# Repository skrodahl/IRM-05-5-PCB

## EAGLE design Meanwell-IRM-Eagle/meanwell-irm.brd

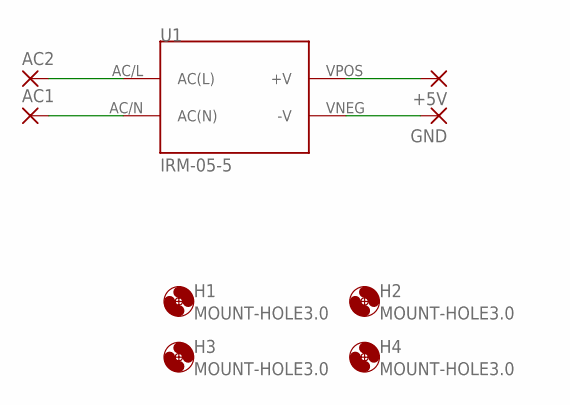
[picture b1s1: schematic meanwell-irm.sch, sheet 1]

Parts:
+5V: 3,81/1,4
AC1, AC2: 3,81/1,4
GND: 3,81/1,4
H1, H2, H3, H4: MOUNT-HOLE3.0; 3,0
U1: IRM-05-5; CONV_IRM-05-5

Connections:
unnamed: AC2.1, U1.AC/L (AC(L))
unnamed: AC1.1, U1.AC/N (AC(N))
unnamed: +5V.1, U1.VPOS (+V)
unnamed: GND.1, U1.VNEG (-V)

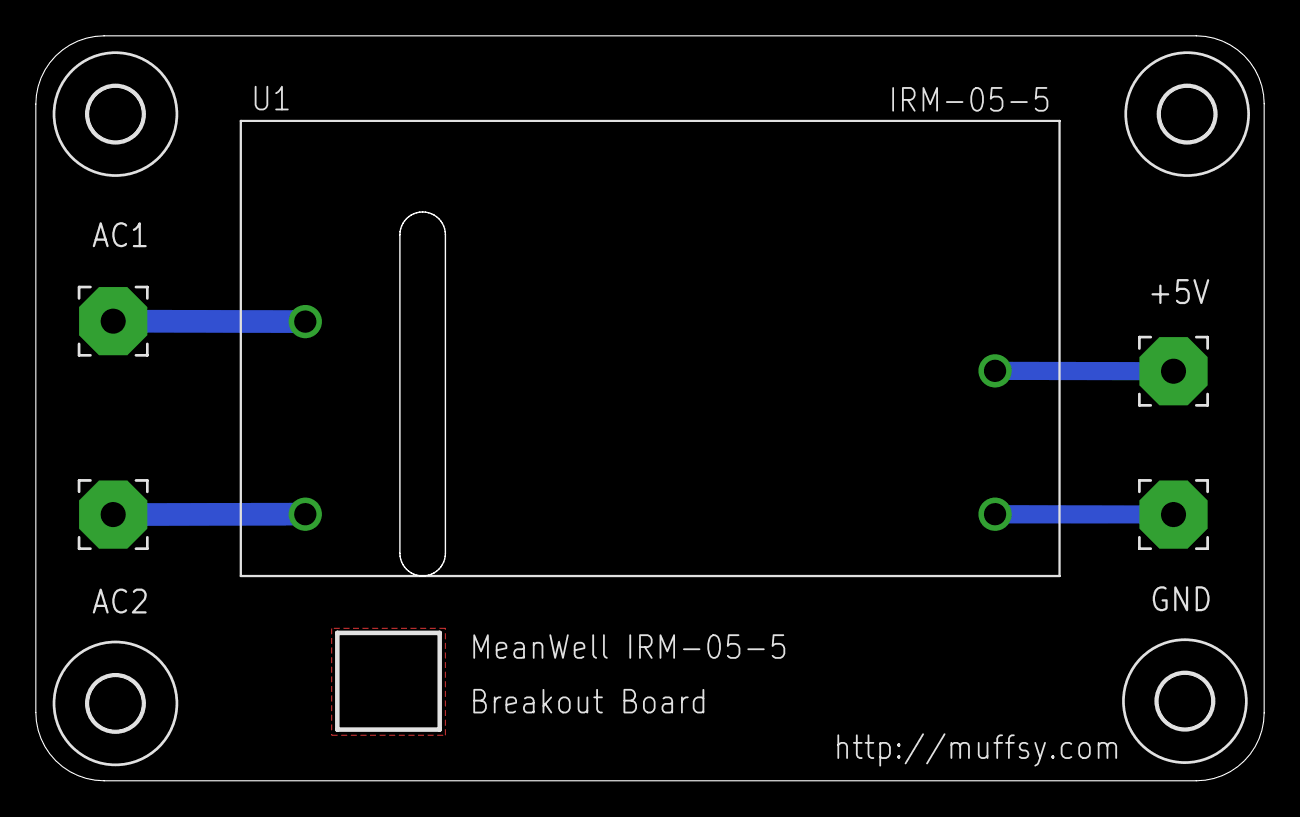
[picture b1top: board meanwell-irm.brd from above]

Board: 2 copper layers, 68.5 x 41.5 mm, 9 parts (0 on the bottom side), 4 nets.

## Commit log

2019-05-13 Eagle Project Files and Gerbers
    Eagle Project files and Gerbers for the 5V MeanWell IRM-05-5 power supply.
